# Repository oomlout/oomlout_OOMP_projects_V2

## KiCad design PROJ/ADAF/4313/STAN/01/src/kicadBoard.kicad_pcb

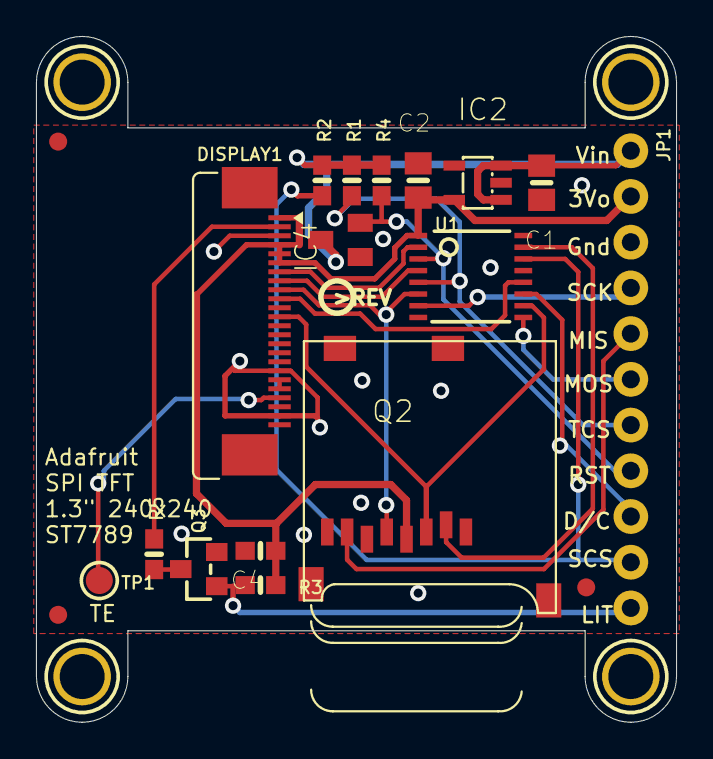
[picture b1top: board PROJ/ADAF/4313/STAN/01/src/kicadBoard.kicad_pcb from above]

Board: 16 copper layers, 35.6 x 38.1 mm, 24 parts (0 on the bottom side), 20 nets.

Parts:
C1, C2: 10uF; 0805-NO
C4: 0.1uF; 0603-NO
DISPLAY1: DISP_LCD_ST7789_1.3IN; TFT_1.3IN_240X240_24P
IC2: AP2112K-3.3; SOT23-5L
IC4: APX803-SAG; SOT23
JP1: 1X11_ROUND_76
Q2: MICROSD
Q3: BSS138; SOT23-WIDE
R1, R2, R4: 10K; 0603-NO
R3: 2.2K; 0603-NO
R5: 10; 0603-NO
TP1: TESTPOINT_ROUND_1.5MM
U1: 74HC4050; TSSOP16
U$2: PCBFEAT-REV-040
U$3, U$4, U$5: FIDUCIAL; FIDUCIAL_1MM
U$7, U$8, U$9, U$10: MOUNTINGHOLE2.5; MOUNTINGHOLE_2.5_PLATED

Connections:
+3V3: C2.1, C4.1, DISPLAY1.1, DISPLAY1.4, DISPLAY1.5, DISPLAY1.6, IC2.5, JP1.2, Q2.4, R3.2, U1.1
BACKLIGHT: JP1.11, Q3.1, R3.1
CARDCS: JP1.10, R2.1, U1.14
CARDCS_3V: Q2.2, U1.15
GND: C1.2, C2.2, C4.2, DISPLAY1.3, DISPLAY1.11, DISPLAY1.13, DISPLAY1.14, DISPLAY1.15, DISPLAY1.16, DISPLAY1.17, DISPLAY1.18, DISPLAY1.19, DISPLAY1.20, DISPLAY1.23, DISPLAY1.24, IC2.2, IC4.1, JP1.3, Q2.6, Q2.MT1, Q2.MT2, Q3.2, U1.8
LEDK: DISPLAY1.2, R5.2
MISO: JP1.5, Q2.7
MOSI: JP1.6, U1.9
MOSI_3V: DISPLAY1.12, Q2.3, U1.10
unnamed: Q3.3, R5.1
RESET: IC4.2, JP1.8, R4.1, U1.3
RESET_3V: DISPLAY1.7, U1.2
SCK: JP1.4, U1.7
SCK_3V: DISPLAY1.9, Q2.5, U1.6
TE: DISPLAY1.21, TP1.P$1
TFTCS: JP1.7, R1.1, U1.5
TFTCS_3V: DISPLAY1.8, U1.4
TFTDC: JP1.9, U1.11
TFTDC_3V: DISPLAY1.10, U1.12
VIN: C1.1, IC2.1, IC2.3, IC4.3, JP1.1, R1.2, R2.2, R4.2

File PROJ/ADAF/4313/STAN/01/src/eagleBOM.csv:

"Part";"Value";"Device";"Package";"Description";"BOM";
"C1";"10uF";"CAP_CERAMIC0805-NOOUTLINE";"0805-NO";"Ceramic Capacitors";"";
"C2";"10uF";"CAP_CERAMIC0805-NOOUTLINE";"0805-NO";"Ceramic Capacitors";"";
"C4";"0.1uF";"CAP_CERAMIC0603_NO";"0603-NO";"Ceramic Capacitors";"";
"DISPLAY1";"DISP_LCD_ST7789_1.3IN";"DISP_LCD_ST7789_1.3IN";"TFT_1.3IN_240X240_24P";"";"";
"IC2";"AP2112K-3.3";"LP298XS";"SOT23-5L";"";"";
"IC4";"APX803-SAG";"AXP083-SAG";"SOT23";"";"";
"JP1";"";"HEADER-1X1176MIL";"1X11_ROUND_76";"";"";
"Q2";"MICROSD";"MICROSD";"MICROSD";"Micro-SD / Transflash card holder with SPI pinout";"";
"Q3";"BSS138";"MOSFET-NWIDE";"SOT23-WIDE";"N-Channel Mosfet";"";
"R1";"10K";"RESISTOR_0603_NOOUT";"0603-NO";"Resistors";"";
"R2";"10K";"RESISTOR_0603_NOOUT";"0603-NO";"Resistors";"";
"R3";"2.2K";"RESISTOR_0603_NOOUT";"0603-NO";"Resistors";"";
"R4";"10K";"RESISTOR_0603_NOOUT";"0603-NO";"Resistors";"";
"R5";"10";"RESISTOR_0603_NOOUT";"0603-NO";"Resistors";"";
"TP1";"";"TESTPOINTROUND1.5MM";"TESTPOINT_ROUND_1.5MM";"Test Point";"";
"U$3";"FIDUCIAL";"FIDUCIAL";"FIDUCIAL_1MM";"For use by pick and place machines to calibrate the vision/machine, 1mm";"";
"U$4";"FIDUCIAL";"FIDUCIAL";"FIDUCIAL_1MM";"For use by pick and place machines to calibrate the vision/machine, 1mm";"";
"U$5";"FIDUCIAL";"FIDUCIAL";"FIDUCIAL_1MM";"For use by pick and place machines to calibrate the vision/machine, 1mm";"";
"U$7";"MOUNTINGHOLE2.5";"MOUNTINGHOLE2.5";"MOUNTINGHOLE_2.5_PLATED";"Mounting Hole";"EXCLUDE";
"U$8";"MOUNTINGHOLE2.5";"MOUNTINGHOLE2.5";"MOUNTINGHOLE_2.5_PLATED";"Mounting Hole";"EXCLUDE";
"U$9";"MOUNTINGHOLE2.5";"MOUNTINGHOLE2.5";"MOUNTINGHOLE_2.5_PLATED";"Mounting Hole";"EXCLUDE";
"U$10";"MOUNTINGHOLE2.5";"MOUNTINGHOLE2.5";"MOUNTINGHOLE_2.5_PLATED";"Mounting Hole";"EXCLUDE";
"U1";"74HC4050";"74HC4050DTSSOP";"TSSOP16";"6-channel level shifter";"";

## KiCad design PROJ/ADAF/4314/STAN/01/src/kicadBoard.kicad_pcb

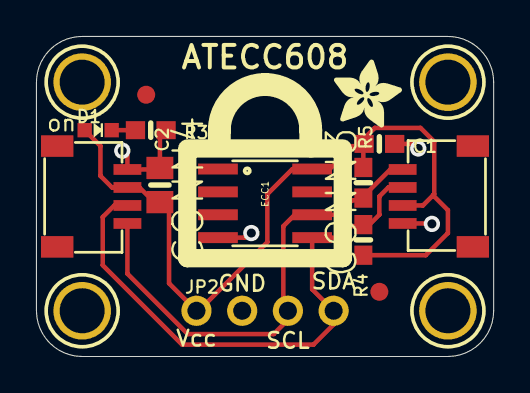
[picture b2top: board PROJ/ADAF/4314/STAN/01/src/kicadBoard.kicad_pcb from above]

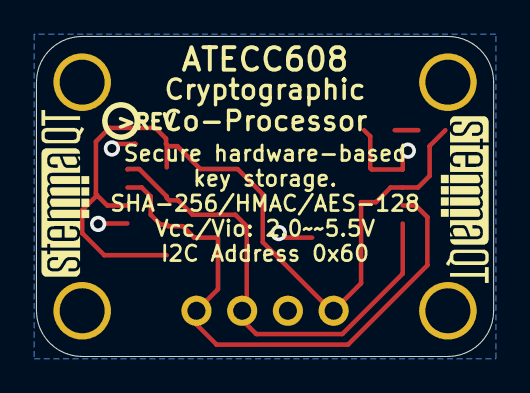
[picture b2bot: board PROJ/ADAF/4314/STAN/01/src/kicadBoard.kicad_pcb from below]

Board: 2 copper layers, 25.4 x 17.8 mm, 20 parts (3 on the bottom side), 5 nets.

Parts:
C1: 0.1uF; 0603-NO
C2: 10uF; 0805-NO
CONN3, CONN4: STEMMA_I2C_QT; JST_SH4
D1: GREEN; CHIPLED_0603_NOOUTLINE
ECC1: ATECC608; SOIC8
FID3, FID4: FIDUCIAL_1MM
JP2: 1X04_ROUND
R3: 4.7K; 0603-NO
R4, R5: 10K; 0603-NO
U$11, U$12, U$14, U$15: MOUNTINGHOLE2.5; MOUNTINGHOLE_2.5_PLATED
U$17: ADAFRUIT_3.5MM
U$18: PCBFEAT-REV-040
U$19, U$20: STEMMAQT

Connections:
GND: C1.2, C2.2, CONN3.1, CONN4.1, ECC1.4, JP2.2, R3.2
unnamed: D1.C, R3.1
SCL: CONN3.4, CONN4.4, ECC1.6, JP2.3, R5.1
SDA: CONN3.3, CONN4.3, ECC1.5, JP2.4, R4.1
VCC: C1.1, C2.1, CONN3.2, CONN4.2, D1.A, ECC1.8, JP2.1, R4.2, R5.2

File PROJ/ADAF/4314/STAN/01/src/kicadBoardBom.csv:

"Id";"Designator";"Package";"Quantity";"Designation";"Supplier and ref";
1;"ECC1";"SOIC8";1;"ATECC608";;;
2;"FID4,FID3";"FIDUCIAL_1MM";2;"FIDUCIAL_1MM";;;
3;"D1";"CHIPLED_0603_NOOUTLINE";1;"GREEN";;;
4;"C2";"0805-NO";1;"10uF";;;
5;"CONN4,CONN3";"JST_SH4";2;"STEMMA_I2C_QT";;;
6;"U$12,U$15,U$11,U$14";"MOUNTINGHOLE_2.5_PLATED";4;"MOUNTINGHOLE2.5";;;
7;"R3";"0603-NO";1;"4.7K";;;
8;"C1";"0603-NO";1;"0.1uF";;;
9;"U$17";"ADAFRUIT_3.5MM";1;"";;;
10;"R4,R5";"0603-NO";2;"10K";;;
11;"JP2";"1X04_ROUND";1;"";;;
12;"U$19,U$20";"STEMMAQT";2;"";;;
13;"U$18";"PCBFEAT-REV-040";1;"";;;

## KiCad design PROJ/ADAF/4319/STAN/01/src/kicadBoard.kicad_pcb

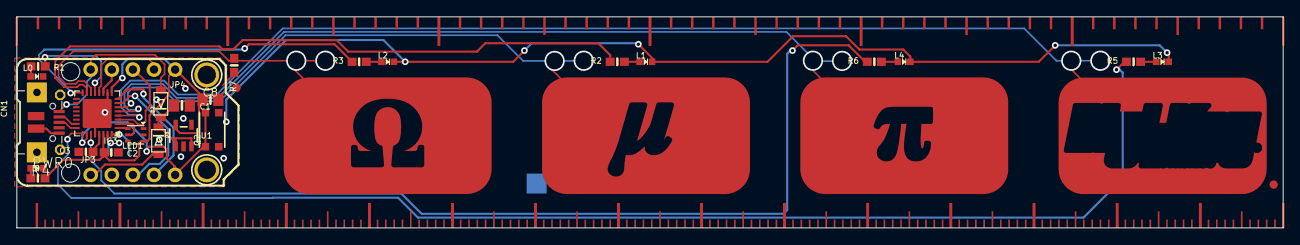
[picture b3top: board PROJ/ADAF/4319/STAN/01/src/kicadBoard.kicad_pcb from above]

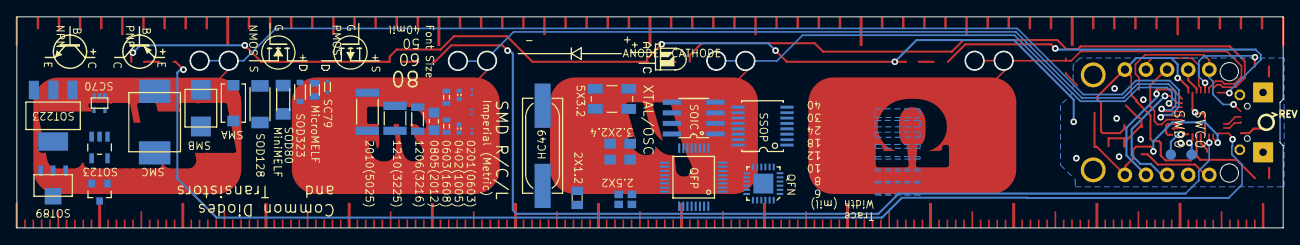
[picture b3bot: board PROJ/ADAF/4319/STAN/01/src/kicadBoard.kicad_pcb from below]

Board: 16 copper layers, 152.4 x 25.4 mm, 98 parts (43 on the bottom side), 30 nets.

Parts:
@HOLE0, @HOLE1: (no value)
C1, C8: 10uF; 0805-NO
C2, C3: 1uF; 0603-NO
CN1: 4U#20329; 4UCONN_20329_NARROW
D2, D3: SCHOTTKY; SOD-123FL
E$1, E$2, E$3, E$4, E$5, E$6, E$7, E$8, E$9, E$10, E$11, E$12, E$13, E$14, E$15: EDGE-MILLIMETERS
E$16, E$60, E$63: 0201
E$17, E$18, E$19, E$20, E$21, E$22: EDGE-INCHES-TENTH
E$23, E$61: 0402
E$24, E$62: 0603
E$25: 0805
E$26: 1206
E$27: 1210
E$28: 2010
E$31: SOT223
E$32: SOT89
E$33: SOT23-5
E$34: SOT23-3
E$35: SC70
E$36: CRYSTAL-SMD-5X3.2
E$37: CRYSTAL-SMD-3.2X2.5
E$38: CRYSTAL-SMD-2.5X2
E$39: HC49UP
E$40: XTAL-2X1.2
E$41: MICROMELF-R
E$42: SC79_INFINEON
E$43: SMA-DIODE
E$44: SMB-DIODE
E$45: SMC
E$47: SOD-128
E$48: SOD-323
E$49: SOD80C
E$50: NMOS-SYMB
E$51: PMOS-SYMB
E$52: DIODE-SYMB
E$53: LED-GUIDE
E$54: NPN-SYMB
E$55: QFN-24
E$56: TSSOP16
E$57: SO08
E$58: TQFP32-5MM
E$59: PNP-SYMB
IC3: ATSAMD21E; QFN32_5MM
JP3, JP4: 1X05_ROUND_70
L0, L2: red; CHIPLED_0603_NOOUTLINE
L1: yellow; CHIPLED_0603_NOOUTLINE
L3: blue; CHIPLED_0603_NOOUTLINE
L4: green; CHIPLED_0603_NOOUTLINE
LED1: AP102-2020; APA102_2020
PWR0: green; CHIPLED_0603_NOOUTLINE
Q2: reset; BTN_KMR2_4.6X2.8
R1, R2, R3: 2.2K; 0603-NO
R4, R5, R6: 10K; 0603-NO
R7: 2M; 0603-NO
SWC0: TPB1,27; B1,27
SWD0: TPB1,27; B1,27
U1: AP2112K-3.3; SOT23-5
U$1, U$6: FIDUCIAL_1MM
U$2: PYRULER_BOTTOM
U$7: PCBFEAT-REV-040
U$8, U$9: MOUNTINGHOLE2.0; MOUNTINGHOLE_2.0_PLATED
U$14: PYRULER_TOP
U$20: TRINKET_M0_TOP

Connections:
3.3V: C2.1, C8.1, IC3.9, IC3.30, JP4.1, LED1.3, R4.2, U1.5
CAP0: IC3.14, R7.1
D0_A4_PA08_SDA: IC3.11, JP4.4
D1_A0_PA02: IC3.3, JP4.3
D2_A1_PA09_SCL_MISO: IC3.12, JP4.2
D3_A3_PA07_RXD_SCK: IC3.8, JP3.4
D4_A2_PA06_TXD_MOSI: IC3.7, JP3.3
D+: CN1.D+, IC3.24
D-: CN1.D-, IC3.23
DOTSTAR_CLOCK: IC3.2, LED1.5
DOTSTAR_DATA: IC3.1, LED1.6
GND: C1.2, C2.2, C3.2, C8.2, CN1.BASE@1, CN1.BASE@2, CN1.GND, CN1.SPRT@1, CN1.SPRT@2, CN1.SPRT@3, CN1.SPRT@4, IC3.10, IC3.28, IC3.33, JP3.2, L0.C, L1.C, L2.C, L3.C, L4.C, LED1.4, PWR0.C, Q2.B, Q2.B', R7.2, U1.2
LED: IC3.13, R1.2
LED4: IC3.16, R3.2
LED5: IC3.15, R2.2
LED6: IC3.27, R6.2
LED7: IC3.25, R5.2
unnamed: L0.A, R1.1
unnamed: IC3.31, SWC0.TP
unnamed: IC3.32, SWD0.TP
unnamed: PWR0.A, R4.1
unnamed: L1.A, R2.1
unnamed: L2.A, R3.1
unnamed: L4.A, R6.1
unnamed: L3.A, R5.1
VBAT: D3.A, JP3.1
VBUS: CN1.VBUS, D2.A, JP4.5
VDDCORE: C3.1, IC3.29
VOUT: C1.1, D2.C, D3.C, U1.1, U1.3
~RESET: IC3.26, JP3.5, Q2.A, Q2.A'

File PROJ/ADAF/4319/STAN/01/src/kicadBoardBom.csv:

"Id";"Designator";"Package";"Quantity";"Designation";"Supplier and ref";
1;"R2,R3,R1";"0603-NO";3;"2.2K";;;
2;"E$19,E$22,E$21,E$20,E$18,E$17";"EDGE-INCHES-TENTH";6;"";;;
3;"JP3,JP4";"1X05_ROUND_70";2;"";;;
4;"PWR0,L4";"CHIPLED_0603_NOOUTLINE";2;"green";;;
5;"U$20";"TRINKET_M0_TOP";1;"";;;
6;"E$15,E$8,E$3,E$7,E$11,E$2,E$10,E$5,E$1,E$12,E$4,E$6,E$14,E$13,E$9";"EDGE-MILLIMETERS";15;"";;;
7;"R6,R5,R4";"0603-NO";3;"10K";;;
8;"LED1";"APA102_2020";1;"AP102-2020";;;
9;"CN1";"4UCONN_20329_NARROW";1;"4U#20329";;;
10;"U$6,U$1";"FIDUCIAL_1MM";2;"FIDUCIAL_1MM";;;
11;"U$9,U$8";"MOUNTINGHOLE_2.0_PLATED";2;"MOUNTINGHOLE2.0";;;
12;"C8,C1";"0805-NO";2;"10uF";;;
13;"L1";"CHIPLED_0603_NOOUTLINE";1;"yellow";;;
14;"U$14";"PYRULER_TOP";1;"";;;
15;"L0,L2";"CHIPLED_0603_NOOUTLINE";2;"red";;;
16;"R7";"0603-NO";1;"2M";;;
17;"L3";"CHIPLED_0603_NOOUTLINE";1;"blue";;;
18;"C3,C2";"0603-NO";2;"1uF";;;
19;"@HOLE0,@HOLE1";"";2;"";;;
20;"D2,D3";"SOD-123FL";2;"SCHOTTKY";;;
21;"IC3";"QFN32_5MM";1;"ATSAMD21E";;;
22;"Q2";"BTN_KMR2_4.6X2.8";1;"reset";;;
23;"U1";"SOT23-5";1;"AP2112K-3.3";;;
24;"E$48";"SOD-323";1;"";;;
25;"E$39";"HC49UP";1;"";;;
26;"E$44";"SMB-DIODE";1;"";;;
27;"U$7";"PCBFEAT-REV-040";1;"";;;
28;"E$51";"PMOS-SYMB";1;"";;;
29;"E$50";"NMOS-SYMB";1;"";;;
30;"E$36";"CRYSTAL-SMD-5X3.2";1;"";;;
31;"E$56";"TSSOP16";1;"";;;
32;"E$61,E$23";"0402";2;"";;;
33;"E$49";"SOD80C";1;"";;;
34;"E$59";"PNP-SYMB";1;"";;;
35;"E$24,E$62";"0603";2;"";;;
36;"E$55";"QFN-24";1;"";;;
37;"E$42";"SC79_INFINEON";1;"";;;
38;"E$27";"1210";1;"";;;
39;"SWD0,SWC0";"B1,27";2;"TPB1,27";;;
40;"E$52";"DIODE-SYMB";1;"";;;
41;"E$43";"SMA-DIODE";1;"";;;
42;"E$47";"SOD-128";1;"";;;
43;"E$35";"SC70";1;"";;;
44;"E$31";"SOT223";1;"";;;
45;"E$60,E$16,E$63";"0201";3;"";;;
46;"E$58";"TQFP32-5MM";1;"";;;
47;"E$25";"0805";1;"";;;
48;"E$40";"XTAL-2X1.2";1;"";;;
49;"E$33";"SOT23-5";1;"";;;
50;"E$45";"SMC";1;"";;;
51;"E$26";"1206";1;"";;;
52;"E$41";"MICROMELF-R";1;"";;;
53;"E$38";"CRYSTAL-SMD-2.5X2";1;"";;;
54;"E$57";"SO08";1;"";;;
55;"E$32";"SOT89";1;"";;;
56;"E$28";"2010";1;"";;;
57;"E$37";"CRYSTAL-SMD-3.2X2.5";1;"";;;
58;"E$34";"SOT23-3";1;"";;;
59;"E$54";"NPN-SYMB";1;"";;;
60;"U$2";"PYRULER_BOTTOM";1;"";;;
61;"E$53";"LED-GUIDE";1;"";;;

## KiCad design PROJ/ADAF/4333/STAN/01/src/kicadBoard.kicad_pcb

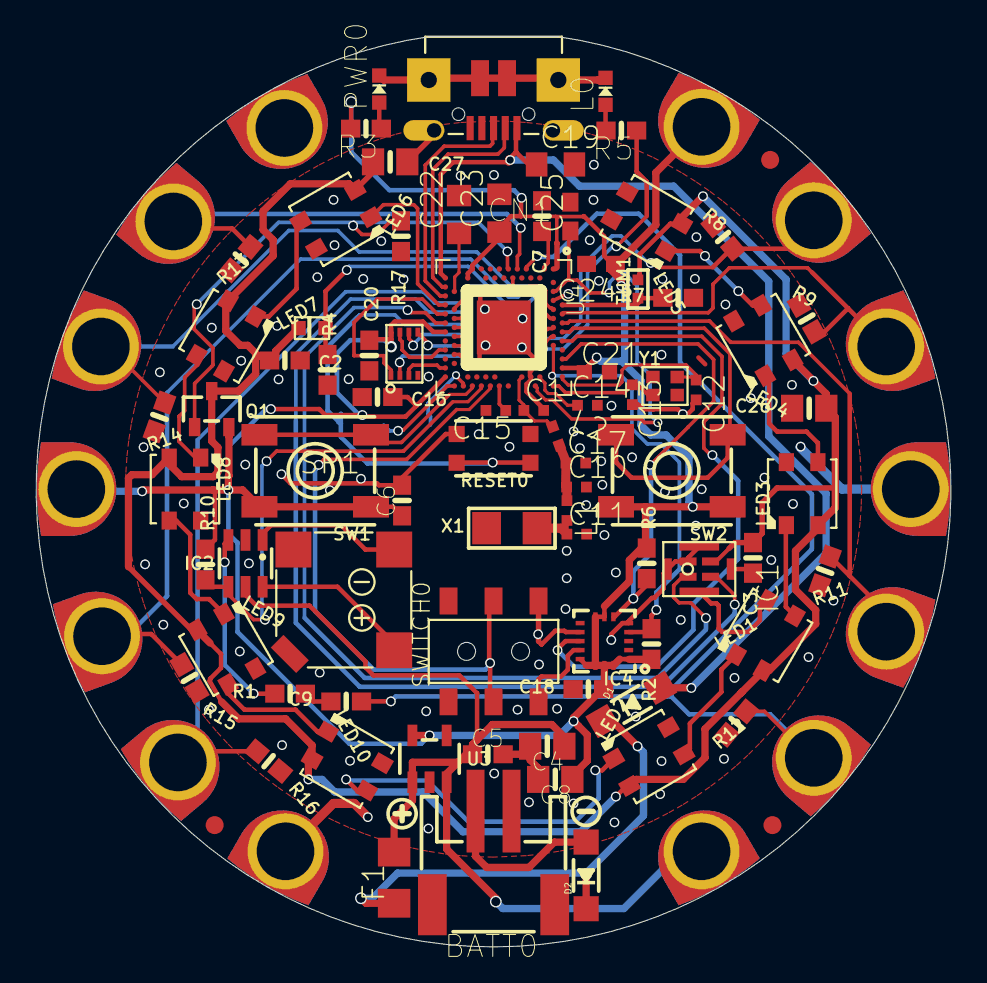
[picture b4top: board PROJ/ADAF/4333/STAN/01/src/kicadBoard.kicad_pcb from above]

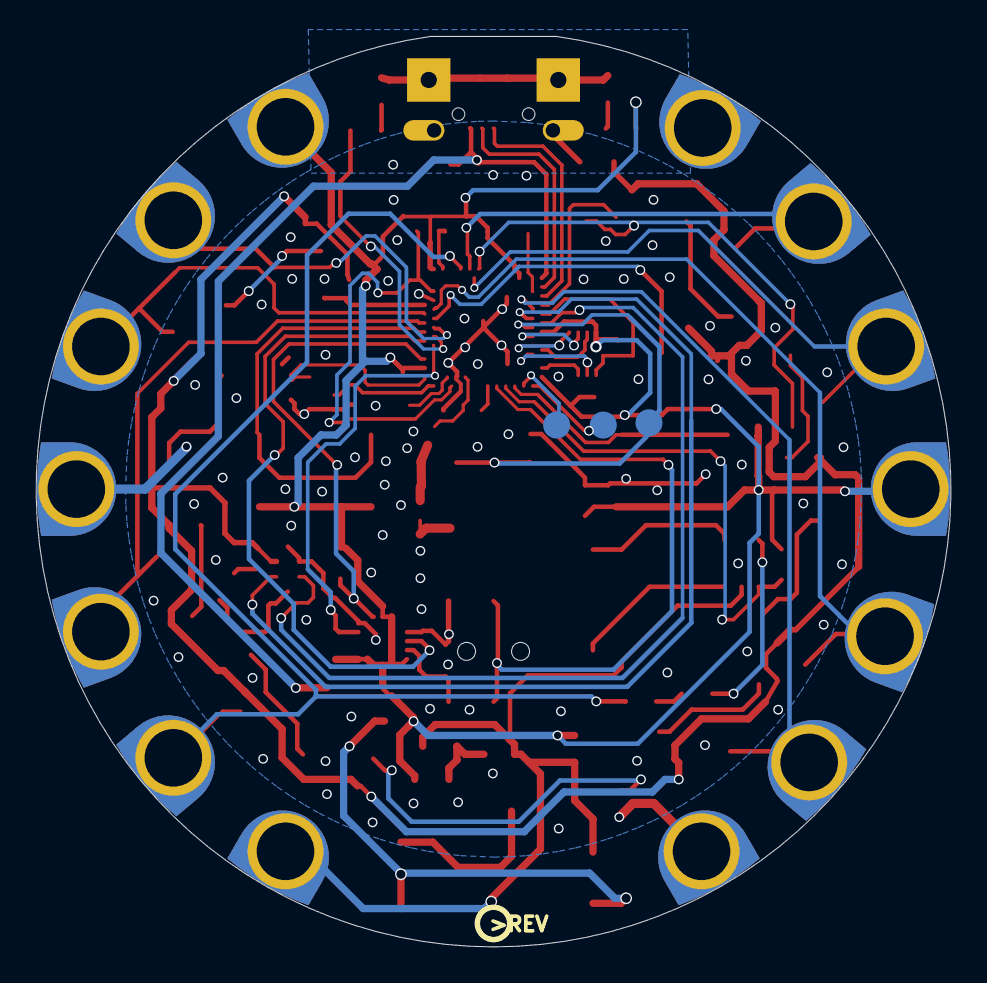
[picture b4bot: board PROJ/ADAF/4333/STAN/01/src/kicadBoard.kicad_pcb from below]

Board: 2 copper layers, 50.8 x 50.6 mm, 104 parts (5 on the bottom side), 65 nets.

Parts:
BATT0: 3-6VDC; JSTPH2
C1, C10, C11, C17: 1pF NP0; RESC0402_N
C2, C3, C5, C6, C18: 1uF; 0603-NO
C4, C8, C26, C27: 10uF; 0805-NO
C7, C16, C20: 0.1uF X7R 10%; 0603-NO
C9: 0.1uF; 0603-NO
C12, C13: 12pF; RESC0402_N
C14: 100pF NP0 5%; RESC0402_N
C15: 820pF NP0 5%; RESC0402_N
C19, C23: 10uF X5R; RESC0805_N
C21: 0.1uF X7R 10%; RESC0603_L
C22: 4.7uF X7S 10%; RESC0805_N
C24, C25: 1uF X7R 10%; RESC0603_N
CN1: MicroB USB; 4UCONN_20329_V2
D1, D2: MBR120; SOD-123
D6: SEWTAP-ALLIGATOR; SEWALLI
F1: 6V+ 500mA; R1206
GND3TAP0: SEWTAP-ALLIGATOR; SEWALLI
GNDTAP0, GNDTAP2: SEWTAP-ALLIGATOR; SEWALLI
IC1: MIC_PDM; SPK0415HM4H
IC2: PAM8301; SOT23-6
IC3: GD25Q16; USON8
IC4: LIS3DH; LGA16_3X3MM
IO9, IO10, IO12: SEWTAP-ALLIGATOR; SEWALLI
L0: RED; CHIPLED_0603_NOOUTLINE
L1, L2: 3.9nH; RESC0402_N
LED1, LED2, LED3, LED4, LED5, LED6, LED7, LED8, LED9, LED10: WS2812B3535; LED3535
PWR0: GREEN; CHIPLED_0603_NOOUTLINE
Q1: DMG3405; SOT23-R
R1: 47K; 0603-NO
R2, R3, R4, R6, R7: 10K; 0603-NO
R5: 4.7K; 0603-NO
R8, R9, R11, R12, R13, R14, R15, R16: 1M; 0603-NO
R10, R17: 100K; 0603-NO
RESET0: KMR2; BTN_KMR2_4.6X2.8
RX0: SEWTAP-ALLIGATOR; SEWALLI
SCL0: SEWTAP-ALLIGATOR; SEWALLI
SDA0: SEWTAP-ALLIGATOR; SEWALLI
SP1: 7.5mm SPK; BUZZER_SMT_7.5MM
SW1, SW2: EVQQ; EVQ-Q2_SMALLER
SWITCH0: EG1390
THM1: THERM; _0402
TP1, TP2, TP3: TESTPOINT_ROUND_1.5MM_NO
TX0: SEWTAP-ALLIGATOR; SEWALLI
U2: ALS-PT19-315C
U3: AP2112K-3.3; SOT23-5
U4: NRF52840; AQFN50P700X800X85_HS-74N_SMALLCENTER
U$1: SYMBOL_MINUS
U$2, U$3, U$6: FIDUCIAL_1MM
U$7: PCBFEAT-REV-040
U$16: CPLAY_BLUEFRUIT_BOT
U$35: SYMBOL_PLUS
U$44: CPLAY_BLUEFRUIT_TOP
UNK3.3VTAP0, UNK3V3TAP2: SEWTAP-ALLIGATOR; SEWALLI
VCC2: SEWTAP-ALLIGATOR; SEWALLI
X1: 2450AT18B100; ANT_2450AT18B100
Y1: 32MHz; CRYSTAL_2X1.6

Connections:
3.3V: C6.1, C8.1, C16.2, C18.1, C20.2, C21.1, C23.1, C24.1, IC3.8, IC4.1, IC4.7, IC4.8, IC4.13, IC4.14, IC4.15, IC4.16, Q1.2, R2.2, R3.2, R6.2, R10.2, SW1.B, SW1.B', SW2.B, SW2.B', U3.5, U4.P$A22, U4.P$AD14, U4.P$AD23, U4.P$B1, U4.P$W1, U4.P$Y2, UNK3.3VTAP0.P$1, UNK3V3TAP2.P$1
A1: D6.P$1, R11.1, U4.P$A12
A2: IO9.P$1, R9.1, U4.P$A10
A3: IO10.P$1, R8.1, U4.P$B13
A4/SCL: R13.1, SCL0.P$1, U4.P$J1
A5/SDA: R14.1, SDA0.P$1, U4.P$K2
D0/A6/RX: R15.1, RX0.P$1, U4.P$B9
D1/TX: R16.1, TX0.P$1, U4.P$AC9
D4_LEFTBUTTON: SW1.A, SW1.A', U4.P$W24
D5_RIGHTBUTTON: SW2.A, SW2.A', U4.P$A14
D7_SLIDESWITCH: SWITCH0.P1, SWITCH0.P2, U4.P$R24
D8_NEOPIX: LED6.1, U4.P$AD8
D11_SPEAKERSD: IC2.4, R10.1, U4.P$U24
D12/SPEAKER: C9.1, IO12.P$1, R12.1, U4.P$G1
D13_LED: R5.1, U4.P$B15
D24_LISIRQ: IC4.11, U4.P$A16
D+: CN1.D+, U4.P$AD6
D-: CN1.D-, U4.P$AD4
DEC1: C7.2, U4.P$C1
DEC3: C14.1, U4.P$D23
DEC4_6: C25.1, U4.P$B5, U4.P$E24
DEC5: C15.1, U4.P$N24
DECUSB: C22.1, U4.P$AC5
GND: BATT0.1, C1.2, C2.2, C3.2, C4.2, C5.2, C6.2, C7.1, C8.2, C10.2, C11.2, C12.2, C13.2, C14.2, C15.2, C16.1, C17.2, C18.2, C19.2, C20.1, C21.2, C22.2, C23.2, C24.2, C25.2, C26.2, C27.2, CN1.BASE@1, CN1.BASE@2, CN1.GND, CN1.SPRT@1, CN1.SPRT@2, CN1.SPRT@3, CN1.SPRT@4, GND3TAP0.P$1, GNDTAP0.P$1, GNDTAP2.P$1, IC1.2, IC1.5, IC1.6, IC1.7, IC1.8, IC2.2, IC3.4, IC4.5, IC4.10, IC4.12, L0.C, LED1.4, LED2.4, LED3.4, LED4.4, LED5.4, LED6.4, LED7.4, LED8.4, LED9.4, LED10.4, PWR0.C, R4.1, R7.1, R8.2, R9.2, R11.2, R12.2, R13.2, R14.2, R15.2, R16.2, R17.2, RESET0.B, RESET0.B', SWITCH0.S1, SWITCH0.S2, U3.2, U4.P$B7, U4.P$F23, U4.THERMPAD
LIGHT: R4.2, U2.E, U4.P$B11
LIS_SCL: IC4.4, R2.1, U4.P$B17
LIS_SDA: IC4.6, R6.1, U4.P$A20
unnamed: PWR0.A, R3.1
unnamed: C1.1, L2.1, U4.P$H23
unnamed: D1.C, D2.C, F1.1
unnamed: C9.2, R1.1
unnamed: BATT0.2, D2.A
unnamed: IC2.3, R1.2
unnamed: IC2.6, SP1.+
unnamed: L0.A, R5.2
unnamed: LED1.1, LED2.3
unnamed: LED1.3, LED3.1
unnamed: LED2.1, LED10.3
unnamed: LED6.3, LED7.1
unnamed: IC2.1, SP1.-
unnamed: LED7.3, LED8.1
unnamed: LED8.3, LED9.1
unnamed: LED9.3, LED10.1
unnamed: LED3.3, LED4.1
unnamed: LED4.3, LED5.1
unnamed: C12.1, U4.P$A23, Y1.3
unnamed: C13.1, U4.P$B24, Y1.1
NEOSENSE_SWITCH: Q1.1, R17.1, U4.P$L1
PDM_CLK: IC1.3, U4.P$AD12
PDM_DAT: IC1.4, U4.P$AC11
QSPI_CS: IC3.1, U4.P$AD10
QSPI_DATA0: IC3.5, U4.P$AC17
QSPI_DATA1: IC3.2, U4.P$AC19
QSPI_DATA2: IC3.3, U4.P$AD22
QSPI_DATA3: IC3.7, U4.P$AD18
QSPI_SCK: IC3.6, U4.P$AC15
RF: C11.1, L1.2, X1.FP
RF1: C10.1, C17.1, L1.1, L2.2
SWCLK: TP1.P$1, U4.P$AA24
SWDIO: TP2.P$1, U4.P$AC24
TEMP_SENSE: R7.2, THM1.1, U4.P$A8
V+: C2.1, C3.1, C26.1, C27.1, IC1.1, LED1.2, LED2.2, LED3.2, LED4.2, LED5.2, LED6.2, LED7.2, LED8.2, LED9.2, LED10.2, Q1.3, THM1.2, U2.C
VBUS: C19.1, CN1.VBUS, D1.A, U4.P$AD2
VCC: C4.1, C5.1, F1.2, IC2.5, U3.1, U3.3, VCC2.P$1
~RESET: RESET0.A, RESET0.A', TP3.P$1, U4.P$AC13

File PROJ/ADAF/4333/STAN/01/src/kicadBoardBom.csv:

"Id";"Designator";"Package";"Quantity";"Designation";"Supplier and ref";
1;"R12,R16,R13,R9,R15,R14,R8,R11";"0603-NO";8;"1M";;;
2;"IO10,SCL0,IO9,IO12,GND3TAP0,UNK3V3TAP2,GNDTAP2,GNDTAP0,RX0,D6,VCC2,UNK3.3VTAP0,TX0,SDA0";"SEWALLI";14;"SEWTAP-ALLIGATOR";;;
3;"LED8,LED4,LED6,LED9,LED7,LED3,LED1,LED2,LED10,LED5";"LED3535";10;"WS2812B3535";;;
4;"CN1";"4UCONN_20329_V2";1;"MicroB USB";;;
5;"C9";"0603-NO";1;"0.1uF";;;
6;"C8,C4,C26,C27";"0805-NO";4;"10uF";;;
7;"R2,R3,R6,R7,R4";"0603-NO";5;"10K";;;
8;"RESET0";"BTN_KMR2_4.6X2.8";1;"KMR2";;;
9;"L2,L1";"RESC0402_N";2;"3.9nH";;;
10;"U$1";"SYMBOL_MINUS";1;"";;;
11;"R17,R10";"0603-NO";2;"100K";;;
12;"IC4";"LGA16_3X3MM";1;"LIS3DH";;;
13;"C14";"RESC0402_N";1;"100pF NP0 5%";;;
14;"R1";"0603-NO";1;"47K";;;
15;"C13,C12";"RESC0402_N";2;"12pF";;;
16;"C5,C18,C2,C3,C6";"0603-NO";5;"1uF";;;
17;"C20,C16,C7";"0603-NO";3;"0.1uF X7R 10%";;;
18;"U$35";"SYMBOL_PLUS";1;"";;;
19;"C15";"RESC0402_N";1;"820pF NP0 5%";;;
20;"C24,C25";"RESC0603_N";2;"1uF X7R 10%";;;
21;"SP1";"BUZZER_SMT_7.5MM";1;"7.5mm SPK";;;
22;"C19,C23";"RESC0805_N";2;"10uF X5R";;;
23;"SW1,SW2";"EVQ-Q2_SMALLER";2;"EVQQ";;;
24;"D1,D2";"SOD-123";2;"MBR120";;;
25;"U2";"ALS-PT19-315C";1;"ALS-PT19-315C";;;
26;"BATT0";"JSTPH2";1;"3-6VDC";;;
27;"U$44";"CPLAY_BLUEFRUIT_TOP";1;"";;;
28;"PWR0";"CHIPLED_0603_NOOUTLINE";1;"GREEN";;;
29;"C22";"RESC0805_N";1;"4.7uF X7S 10%";;;
30;"C21";"RESC0603_L";1;"0.1uF X7R 10%";;;
31;"U$3,U$2,U$6";"FIDUCIAL_1MM";3;"FIDUCIAL_1MM";;;
32;"C1,C17,C11,C10";"RESC0402_N";4;"1pF NP0";;;
33;"IC2";"SOT23-6";1;"PAM8301";;;
34;"Y1";"CRYSTAL_2X1.6";1;"32MHz";;;
35;"U3";"SOT23-5";1;"AP2112K-3.3";;;
36;"R5";"0603-NO";1;"4.7K";;;
37;"IC3";"USON8";1;"GD25Q16";;;
38;"Q1";"SOT23-R";1;"DMG3405";;;
39;"L0";"CHIPLED_0603_NOOUTLINE";1;"RED";;;
40;"THM1";"_0402";1;"THERM";;;
41;"F1";"R1206";1;"6V+ 500mA";;;
42;"IC1";"SPK0415HM4H";1;"MIC_PDM";;;
43;"SWITCH0";"EG1390";1;"EG1390";;;
44;"X1";"ANT_2450AT18B100";1;"2450AT18B100";;;
45;"U4";"AQFN50P700X800X85_HS-74N_SMALLCENTER";1;"NRF52840";;;
46;"TP2,TP3,TP1";"TESTPOINT_ROUND_1.5MM_NO";3;"";;;
47;"U$16";"CPLAY_BLUEFRUIT_BOT";1;"";;;
48;"U$7";"PCBFEAT-REV-040";1;"";;;

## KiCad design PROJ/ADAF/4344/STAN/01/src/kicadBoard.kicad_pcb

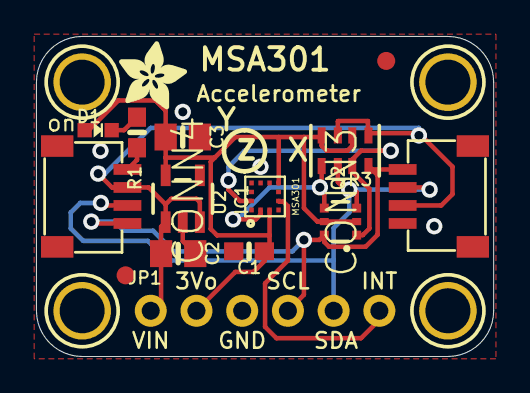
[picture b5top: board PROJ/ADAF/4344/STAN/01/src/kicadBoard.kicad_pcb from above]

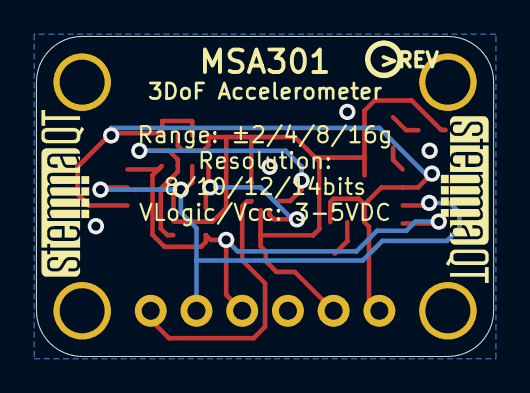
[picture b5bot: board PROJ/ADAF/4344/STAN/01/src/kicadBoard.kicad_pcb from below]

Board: 2 copper layers, 25.4 x 17.8 mm, 22 parts (3 on the bottom side), 9 nets.

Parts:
C1: 0.1uF; 0603-NO
C2, C3: 10uF; 0805-NO
CONN3, CONN4: STEMMA_I2C_QT; JST_SH4
D1: GREEN; CHIPLED_0603_NOOUTLINE
FID3, FID4: FIDUCIAL_1MM
IC1: MSA301; LGA12_2X2MM
JP1: 1X06_ROUND_70
Q2: BSS138; SOT363
R1: 4.7K; 0603-NO
R3: 10K; RESPACK_4X0603
U2: AP2112K-3.3; SOT23-5
U$1, U$17, U$19, U$21: MOUNTINGHOLE2.5; MOUNTINGHOLE_2.5_PLATED
U$22: ADAFRUIT_3.5MM
U$25: PCBFEAT-REV-040
U$30, U$31: STEMMAQT

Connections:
3.3V: C1.1, C3.1, D1.A, IC1.3, IC1.7, JP1.2, Q2.2, Q2.5, R3.2, R3.4, U2.5
GND: C1.2, C2.2, C3.2, CONN3.1, CONN4.1, IC1.9, JP1.3, R1.2, U2.2
INT: IC1.5, JP1.6
unnamed: D1.C, R1.1
SCL: CONN3.4, CONN4.4, JP1.4, Q2.6, R3.8
SCL_3V: IC1.12, Q2.1, R3.7
SDA: CONN3.3, CONN4.3, JP1.5, Q2.3, R3.6
SDA_3V: IC1.2, Q2.4, R3.5
VCC: C2.1, CONN3.2, CONN4.2, JP1.1, R3.1, R3.3, U2.1, U2.3

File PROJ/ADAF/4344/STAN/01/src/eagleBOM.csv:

"Part";"Value";"Device";"Package";"Description";"BOM";
"C1";"0.1uF";"CAP_CERAMIC0603_NO";"0603-NO";"Ceramic Capacitors";"";
"C2";"10uF";"CAP_CERAMIC0805-NOOUTLINE";"0805-NO";"Ceramic Capacitors";"";
"C3";"10uF";"CAP_CERAMIC0805-NOOUTLINE";"0805-NO";"Ceramic Capacitors";"";
"CONN3";"STEMMA_I2C_QT";"STEMMA_I2C_QT";"JST_SH4";"";"";
"CONN4";"STEMMA_I2C_QT";"STEMMA_I2C_QT";"JST_SH4";"";"";
"D1";"GREEN";"LED0603_NOOUTLINE";"CHIPLED_0603_NOOUTLINE";"LED";"";
"FID3";"FIDUCIAL_1MM";"FIDUCIAL_1MM";"FIDUCIAL_1MM";"Fiducial Alignment Points";"EXCLUDE";
"FID4";"FIDUCIAL_1MM";"FIDUCIAL_1MM";"FIDUCIAL_1MM";"Fiducial Alignment Points";"EXCLUDE";
"IC1";"MSA301";"MSA301";"LGA12_2X2MM";"";"";
"JP1";"";"HEADER-1X670MIL";"1X06_ROUND_70";"PIN HEADER";"";
"Q2";"BSS138";"MOSFET-N_DUAL";"SOT363";"Dual N-Channel MOSFET";"";
"R1";"4.7K";"RESISTOR_0603_NOOUT";"0603-NO";"Resistors";"";
"R3";"10K";"RESISTOR_4PACK";"RESPACK_4X0603";"Resistor Packs (4 resistors)";"";
"U$1";"MOUNTINGHOLE2.5";"MOUNTINGHOLE2.5";"MOUNTINGHOLE_2.5_PLATED";"Mounting Hole";"EXCLUDE";
"U$17";"MOUNTINGHOLE2.5";"MOUNTINGHOLE2.5";"MOUNTINGHOLE_2.5_PLATED";"Mounting Hole";"EXCLUDE";
"U$19";"MOUNTINGHOLE2.5";"MOUNTINGHOLE2.5";"MOUNTINGHOLE_2.5_PLATED";"Mounting Hole";"EXCLUDE";
"U$21";"MOUNTINGHOLE2.5";"MOUNTINGHOLE2.5";"MOUNTINGHOLE_2.5_PLATED";"Mounting Hole";"EXCLUDE";
"U2";"AP2112K-3.3";"VREG_SOT23-5";"SOT23-5";"SOT23-5 Fixed Voltage Regulators";"";

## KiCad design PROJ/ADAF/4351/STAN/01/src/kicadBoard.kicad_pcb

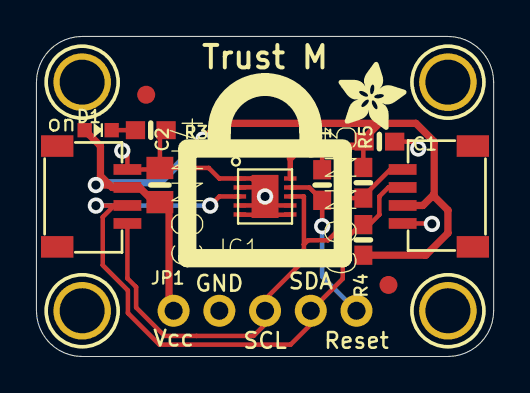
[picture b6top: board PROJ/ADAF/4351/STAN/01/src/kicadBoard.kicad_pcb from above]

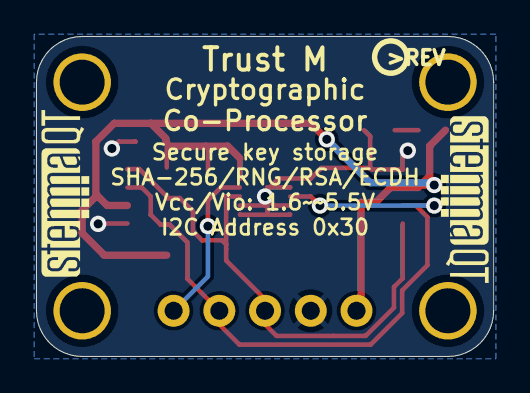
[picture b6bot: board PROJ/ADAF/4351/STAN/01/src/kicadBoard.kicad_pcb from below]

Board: 2 copper layers, 25.4 x 17.8 mm, 21 parts (3 on the bottom side), 6 nets.

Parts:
C1: 0.1uF; 0603-NO
C2: 10uF; 0805-NO
CONN3, CONN4: STEMMA_I2C_QT; JST_SH4
D1: GREEN; CHIPLED_0603_NOOUTLINE
FID3, FID4: FIDUCIAL_1MM
IC1: PG-USON10-10-2
JP1: 1X05_ROUND_70
R1, R3, R4, R5: 10K; 0603-NO
U$11, U$12, U$14, U$15: MOUNTINGHOLE2.5; MOUNTINGHOLE_2.5_PLATED
U$17: ADAFRUIT_3.5MM
U$18: PCBFEAT-REV-040
U$19, U$20: STEMMAQT

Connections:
GND: C1.2, C2.2, CONN3.1, CONN4.1, IC1.1, IC1.2, IC1.4, IC1.5, IC1.6, IC1.7, IC1.THERM, JP1.2, R3.2
unnamed: D1.C, R3.1
RESET: IC1.9, JP1.5, R1.1
SCL: CONN3.4, CONN4.4, IC1.8, JP1.3, R5.1
SDA: CONN3.3, CONN4.3, IC1.3, JP1.4, R4.1
VCC: C1.1, C2.1, CONN3.2, CONN4.2, D1.A, IC1.10, JP1.1, R1.2, R4.2, R5.2

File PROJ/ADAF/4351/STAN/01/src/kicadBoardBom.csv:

"Id";"Designator";"Package";"Quantity";"Designation";"Supplier and ref";
1;"CONN4,CONN3";"JST_SH4";2;"STEMMA_I2C_QT";;;
2;"D1";"CHIPLED_0603_NOOUTLINE";1;"GREEN";;;
3;"IC1";"PG-USON10-10-2";1;"";;;
4;"U$14,U$11,U$12,U$15";"MOUNTINGHOLE_2.5_PLATED";4;"MOUNTINGHOLE2.5";;;
5;"FID4,FID3";"FIDUCIAL_1MM";2;"FIDUCIAL_1MM";;;
6;"C1";"0603-NO";1;"0.1uF";;;
7;"C2";"0805-NO";1;"10uF";;;
8;"R5,R3,R4,R1";"0603-NO";4;"10K";;;
9;"U$17";"ADAFRUIT_3.5MM";1;"";;;
10;"JP1";"1X05_ROUND_70";1;"";;;
11;"U$19,U$20";"STEMMAQT";2;"";;;
12;"U$18";"PCBFEAT-REV-040";1;"";;;

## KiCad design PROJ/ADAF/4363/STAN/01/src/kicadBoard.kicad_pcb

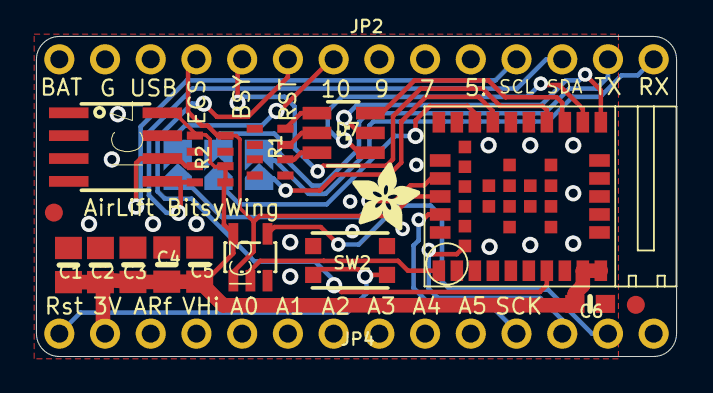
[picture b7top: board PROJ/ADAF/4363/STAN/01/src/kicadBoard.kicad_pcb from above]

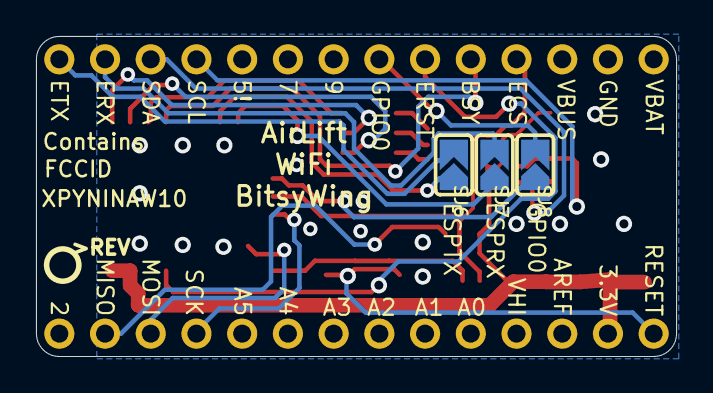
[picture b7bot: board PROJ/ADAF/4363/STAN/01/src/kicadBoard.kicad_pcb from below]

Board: 2 copper layers, 35.6 x 17.8 mm, 22 parts (4 on the bottom side), 24 nets.

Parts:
C1, C2, C3, C4, C5: 10uF; 0805-NO
C6: 0.1uF; 0603-NO
D7: RGBLED_3535_PLCC6
IC3: 74AHC1G125; SOT23-5L
IC4: ATECCX08; SOIC8_150MIL
JP2, JP4: 1X14_ROUND70
R1: 1K; RESPACK_4X0603_NO
R2: 10K; RESPACK_4X0603_NO
SJ6, SJ7, SJ8: SOLDERJUMPER_ARROW_NOPASTE
SW2: KMR2; BTN_KMR2_4.6X2.8
U5: NINA-W102; ARDUINO-UCS&SOCS_NINA-W1X
U$6: PCBFEAT-REV-040
U$34, U$35: FIDUCIAL_1MM
U$62: ADAFRUIT_3.5MM

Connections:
3.3V: C1.1, C2.1, C3.1, C4.1, C5.1, C6.1, IC3.5, IC4.8, JP4.13, R2.1, R2.5, R2.6, U5.9, U5.10
BLUE: D7.6, U5.18
ERX: JP2.13, SJ7.2
ESP_BUSY: JP2.6, U5.7
ESP_CS: IC3.1, JP2.4, R2.8, U5.28
ESP_GPIO0: SJ8.1, U5.27
ESP_MISO: IC3.2, U5.1
ESP_RESET: JP2.5, U5.19
ESP_RX: SJ7.1, U5.23
ESP_TX: SJ6.1, U5.22
ETX: JP2.14, SJ6.2
GND: C1.2, C2.2, C3.2, C4.2, C5.2, C6.2, IC3.3, IC4.4, JP2.2, R1.5, R1.6, R1.7, SW2.A, SW2.A', U5.6, U5.12, U5.14, U5.26, U5.30, U5.GND@1, U5.GND@2, U5.GND@3, U5.GND@4, U5.GND@5, U5.GND@6, U5.GND@7, U5.GND@8, U5.GND@9, U5.GND@10, U5.GND@11, U5.GND@12
GPIO0: JP2.7, SJ8.2
GREEN: D7.5, U5.16
MISO: IC3.4, JP4.2
MOSI: JP4.3, U5.31
unnamed: D7.1, R1.4
unnamed: D7.2, R1.3
unnamed: D7.3, R1.2
RED: D7.4, U5.17
SCK: JP4.4, U5.29
SCL: IC4.6, JP2.11, R2.3
SDA: IC4.5, JP2.12, R2.4
~RESET: JP4.14, SW2.B, SW2.B'

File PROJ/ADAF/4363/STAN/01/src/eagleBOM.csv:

"Part";"Value";"Device";"Package";"Description";"BOM";"CODE-ARDUINO";"DATASHEET";"DISTRIBUTOR-LINK";"DISTRIBUTOR-PN";"MANUFACTURER";"MANUFACTURER-PN";"VALUE";
"C1";"10uF";"CAP_CERAMIC0805-NOOUTLINE";"0805-NO";"Ceramic Capacitors";"";"";"";"";"";"";"";"";
"C2";"10uF";"CAP_CERAMIC0805-NOOUTLINE";"0805-NO";"Ceramic Capacitors";"";"";"";"";"";"";"";"";
"C3";"10uF";"CAP_CERAMIC0805-NOOUTLINE";"0805-NO";"Ceramic Capacitors";"";"";"";"";"";"";"";"";
"C4";"10uF";"CAP_CERAMIC0805-NOOUTLINE";"0805-NO";"Ceramic Capacitors";"";"";"";"";"";"";"";"";
"C5";"10uF";"CAP_CERAMIC0805-NOOUTLINE";"0805-NO";"Ceramic Capacitors";"";"";"";"";"";"";"";"";
"C6";"0.1uF";"CAP_CERAMIC0603_NO";"0603-NO";"Ceramic Capacitors";"";"";"";"";"";"";"";"";
"D7";"";"LED_RGB_PLCC63535";"RGBLED_3535_PLCC6";"RGB LED";"";"";"";"";"";"";"";"";
"IC3";"74AHC1G125";"74AHC1G125";"SOT23-5L";"";"";"";"";"";"";"";"";"";
"IC4";"ATECCX08";"ATECCX08";"SOIC8_150MIL";"";"";"";"";"";"";"";"";"";
"JP2";"";"HEADER-1X14";"1X14_ROUND70";"";"";"";"";"";"";"";"";"";
"JP4";"";"HEADER-1X14";"1X14_ROUND70";"";"";"";"";"";"";"";"";"";
"R1";"1K";"RESISTOR_4PACK_NO";"RESPACK_4X0603_NO";"Resistor Packs (4 resistors)";"";"";"";"";"";"";"";"";
"R2";"10K";"RESISTOR_4PACK_NO";"RESPACK_4X0603_NO";"Resistor Packs (4 resistors)";"";"";"";"";"";"";"";"";
"SJ6";"";"SOLDERJUMPER";"SOLDERJUMPER_ARROW_NOPASTE";"SMD Solder JUMPER";"EXCLUDE";"";"";"";"";"";"";"";
"SJ7";"";"SOLDERJUMPER";"SOLDERJUMPER_ARROW_NOPASTE";"SMD Solder JUMPER";"EXCLUDE";"";"";"";"";"";"";"";
"SJ8";"";"SOLDERJUMPER";"SOLDERJUMPER_ARROW_NOPASTE";"SMD Solder JUMPER";"EXCLUDE";"";"";"";"";"";"";"";
"SW2";"KMR2";"SWITCH_TACT_SMT4.6X2.8";"BTN_KMR2_4.6X2.8";"SMT Tact Switches";"";"";"";"";"";"";"";"";
"U$34";"FIDUCIAL_1MM";"FIDUCIAL_1MM";"FIDUCIAL_1MM";"Fiducial Alignment Points";"EXCLUDE";"";"";"";"";"";"";"";
"U$35";"FIDUCIAL_1MM";"FIDUCIAL_1MM";"FIDUCIAL_1MM";"Fiducial Alignment Points";"EXCLUDE";"";"";"";"";"";"";"";
"U5";"NINA-W102";"NINA-W10X-102NINA-W10X";"ARDUINO-UCS&SOCS_NINA-W1X";"uBlox NINA-W10X ESP32 WiFi/BLE module";"";"2205";"https://www.u-blox.com/sites/default/files/NINA-W1_DataSheet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";"https://www.digikey.com/product-detail/en/u-blox-america-inc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";"672-1070-1-ND";"Ublocks";"NINA-W102";"NINA-W102";

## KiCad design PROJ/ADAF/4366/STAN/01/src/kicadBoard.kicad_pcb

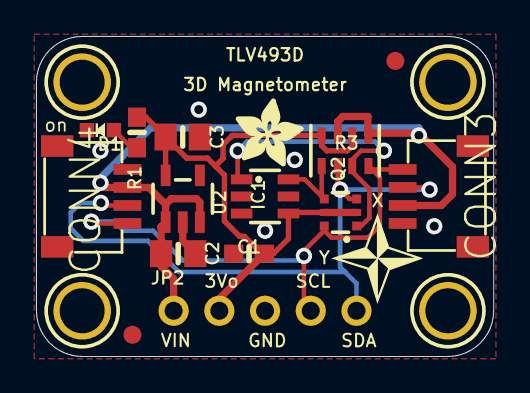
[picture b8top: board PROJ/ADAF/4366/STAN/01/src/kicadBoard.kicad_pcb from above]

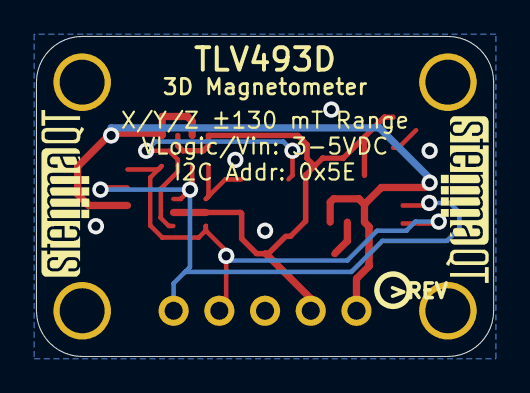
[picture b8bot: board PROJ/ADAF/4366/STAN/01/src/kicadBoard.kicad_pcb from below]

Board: 2 copper layers, 25.4 x 17.8 mm, 24 parts (4 on the bottom side), 8 nets.

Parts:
C1: 0.1uF; 0603-NO
C2, C3: 10uF; 0805-NO
CONN3, CONN4: STEMMA_I2C_QT; JST_SH4
D1: GREEN; CHIPLED_0603_NOOUTLINE
FID3, FID4: FIDUCIAL_1MM
IC1: TLV493D; SOT23-6
JP2: 1X05_ROUND
Q2: BSS138; SOT363
R1: 10K; 0603-NO
R3: 10K; RESPACK_4X0603
U2: AP2112K-3.3; SOT23-5
U$1, U$17, U$19, U$21: MOUNTINGHOLE2.5; MOUNTINGHOLE_2.5_PLATED
U$2: SYMBOL_COMPASSXY_5MM
U$4: KATTNI_STOP
U$22: ADAFRUIT_3.5MM
U$25: PCBFEAT-REV-040
U$30, U$31: STEMMAQT

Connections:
3.3V: C1.1, C3.1, IC1.4, JP2.2, Q2.2, Q2.5, R1.1, R3.2, R3.4, U2.5
GND: C1.2, C2.2, C3.2, CONN3.1, CONN4.1, D1.C, IC1.2, IC1.3, IC1.5, JP2.3, U2.2
unnamed: D1.A, R1.2
SCL: CONN3.4, CONN4.4, JP2.4, Q2.6, R3.8
SCL_3V: IC1.1, Q2.1, R3.7
SDA: CONN3.3, CONN4.3, JP2.5, Q2.3, R3.6
SDA_3V: IC1.6, Q2.4, R3.5
VCC: C2.1, CONN3.2, CONN4.2, JP2.1, R3.1, R3.3, U2.1, U2.3
